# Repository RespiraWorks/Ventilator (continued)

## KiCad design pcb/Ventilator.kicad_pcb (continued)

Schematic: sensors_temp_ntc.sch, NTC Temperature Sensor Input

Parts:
C63: 10uF; C_1210_3225Metric; Voltage 100V; Manufacturer PN GRM32EC72A106KE05L
J31: Temperature sensor (NTC); Molex_Micro-Fit_3.0_43650-0215_1x02_P3.00mm_Vertical; Manufacturer PN 43650-0215
R102: 220 0.1%; R_0603_1608Metric; Manufacturer PN RG1608P-221-B-T5
R103: 10k 0.1%; R_0603_1608Metric; Manufacturer PN RG1608P-103-B-T5
U11: USBLC6-2SC6; SOT-23-6; Manufacturer PN USBLC6-2SC6

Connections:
+3.3V_Sns: R102.2, U11.5; also elsewhere on the board
GND: C63.2, R103.1, U11.2; also elsewhere on the board
unnamed: J31.1, U11.1
unnamed: J31.2, U11.3
unnamed: R102.1, U11.6

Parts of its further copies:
C60, C61, C62, C64: 10uF; C_1210_3225Metric; Voltage 100V; Manufacturer PN GRM32EC72A106KE05L
J32, J33, J34, J35: Temperature sensor (NTC); Molex_Micro-Fit_3.0_43650-0215_1x02_P3.00mm_Vertical; Manufacturer PN 43650-0215
R104, R106, R108, R110: 220 0.1%; R_0603_1608Metric; Manufacturer PN RG1608P-221-B-T5
R105, R107, R109, R111: 10k 0.1%; R_0603_1608Metric; Manufacturer PN RG1608P-103-B-T5
U12, U13, U14, U15: USBLC6-2SC6; SOT-23-6; Manufacturer PN USBLC6-2SC6

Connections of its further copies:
+3.3V_Sns: R104.2, R106.2, R108.2, R110.2, U12.5, U13.5, U14.5, U15.5; also elsewhere on the board
/System Monitor ADC/ADC1: C61.1, R105.2, U12.4; also elsewhere on the board
/System Monitor ADC/ADC2: C62.1, R107.2, U13.4; also elsewhere on the board
/System Monitor ADC/ADC4: C64.1, R111.2, U15.4; also elsewhere on the board
GND: C60.2, C61.2, C62.2, C64.2, R105.1, R107.1, R109.1, R111.1, U12.2, U13.2, U14.2, U15.2; also elsewhere on the board
unnamed: J32.1, U12.1
unnamed: J32.2, U12.3
unnamed: J33.1, U13.1
unnamed: J33.2, U13.3
unnamed: J34.1, U14.1
unnamed: J34.2, U14.3
unnamed: J35.1, U15.1
unnamed: J35.2, U15.3
unnamed: R104.1, U12.6
unnamed: R106.1, U13.6
unnamed: R108.1, U14.6
unnamed: R110.1, U15.6

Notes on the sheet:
LPF varies with temp (30hz at 150C, 3.1hz at 25C, 2.2hz at 0C) OK because of large margin between ADC sampling rate and desired sensor bandwidth
for 10k NTC B=3380K: @150C: R = 350 Vout = 3.12V Sensitivity: 2mV/degC @100C: R = 1022 Vout = 2.94V Sensitivity: 6mV/degC @25C: R = 10000 Vout = 1.63V Sensitivity: 30mV/degC @0C: R = 28255 Vout = 0.86V Sensitivity: 29mV/degC Temp (C) = B / ( ln( Vcc*10k/Vout/Rlim - (10k+220)/Rlim ) ) + 273.15 Where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
NTC placed on the high side of divider so that NTC missing or break does not drive ADC input to VCC Peak self-heating is 0.2mW, glass bead thermistor in air is about 1.5mW/degC, so this is a max error of 0.13degC due to self-heating.
Short current limit
150 nA max. leakage adds << 1 degree error across full temp. range

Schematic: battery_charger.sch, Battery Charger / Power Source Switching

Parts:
C98: 1nF; C_0603_1608Metric
C99, C109: 47nF; C_0603_1608Metric; Voltage 50V; Manufacturer PN C0603C473K5RACTU
C100, C101, C102, C111, C112, C113: 100nF; C_0603_1608Metric; Voltage 50V; Manufacturer PN C0603C104K5RACTU
C103, C106, C117: 10nF; C_0603_1608Metric; Voltage 50V; Manufacturer PN GRM1885C1H103JA01D
C104, C107, C116, C118, C119, C121, C122, C123, C124, C125: 10uF; C_1210_3225Metric; Voltage 100V; Manufacturer PN GRM32EC72A106KE05L
C105, C110: 1uF; C_0603_1608Metric; Voltage 50V; Manufacturer PN C0805C105K5RACTU
C108, C114, C115, C120: 100pF; C_0603_1608Metric; Voltage 50V; Manufacturer PN C0603C101J5GACTU
C126, C127: 33uF; CP_Elec_6.3x7.7; Voltage 50V; Manufacturer PN EEE-FK1H330XP
D27, D28: BAT54J; D_SOD-323F; Manufacturer PN BAT54J,115
HS1, HS2, HS3, HS4: Heatsink_Pad; Heatsink_Aavid_573100D00010G_HandSolder; Part Number 573100D00010G
L3: SRP1038A-3R3M; L_Bourns-SRP1038; Manufacturer PN SRP1038A-3R3M
Q16, Q17, Q18, Q19: BSC065N06LS5ATMA1; VSONP-8-1EP_5x6_P1.27mm; Manufacturer PN BSC065N06LS5ATMA1
Q20: SI7145DP-T1-GE3; VSONP-8-1EP_5x6_P1.27mm; Manufacturer PN SI7145DP-T1-GE3
R169: 442k; R_0603_1608Metric
R170, R172, R176: 100k; R_0603_1608Metric
R171, R175: 316k; R_0603_1608Metric
R173, R188: 0.01; R_1206_3216Metric; Manufacturer PN WSL1206R0100FEA
R174: 10; R_0603_1608Metric
R177, R178, R184, R186: 0; R_0603_1608Metric
R179, R180: 4.02k; R_0603_1608Metric
R181, R182, R185: 10k; R_0603_1608Metric
R183: 3M; R_0603_1608Metric
R187: 30.1k; R_0603_1608Metric
U23: BQ24773; QFN-28-1EP_4x4mm_P0.4mm_EP2.6x2.6mm_ThermalVias; Manufacturer PN BQ24773RUYR

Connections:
+3.3V_Ctrl: R181.2, R185.1; also elsewhere on the board
/CC-SCL: U23.12; also elsewhere on the board
/CC-SDA: U23.11; also elsewhere on the board
/PMon-ACOK: R185.2, U23.5; also elsewhere on the board
/PMon-PSys: C114.1, R187.1, U23.9; also elsewhere on the board
/Power Entry / Battery Handling/Battery Charger / Source Switching/Buck-In: C101.2, C102.1, C104.1, C107.1, HS3.1, Q18.3, R173.1, R177.1
/Power Entry / Battery Handling/Battery Charger / Source Switching/Pack-P: D27.2 (A), HS4.1, Q20.3, R175.1, U23.17; also elsewhere on the board
/Power Entry / Battery Handling/Battery Charger / Source Switching/RegN: C110.1, R171.1, R182.2, U23.24
/Power Entry / Battery Handling/Battery Charger / Source Switching/Vin-Adp-Swit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: C100.1, C101.1, HS2.1, Q17.3, R173.2, R178.2
/Power Entry / Battery Handling/PMon-IAdp: C120.1, U23.7; also elsewhere on the board
/Power Entry / Battery Handling/PMon-IBat: C115.1, U23.8; also elsewhere on the board
/Power Entry / Battery Handling/Power-Sw-P: C111.1, C113.1, C116.1, C117.1, C118.1, C119.1, C121.1, C122.1, C123.1, C124.1, C125.1, C126.1, C127.1, L3.2, R188.2, U23.20; also elsewhere on the board
/Power Entry / Battery Handling/Vin-Adp: C98.1, D28.2 (A), HS1.1, Q16.3, R169.1; also elsewhere on the board
GND: C100.2, C102.2, C103.2, C104.2, C105.2, C106.2, C107.2, C108.1, C110.2, C111.2, C112.1, C114.2, C115.2, C116.2, C117.2, C118.2, C119.2, C120.2, C121.2, C122.2, C123.2, C124.2, C125.2, C126.2, C127.2, Q19.1, R170.2, R172.2, R176.2, R187.2, U23.22, U23.29; also elsewhere on the board
unnamed: C98.2, C99.2, Q16.2, Q17.2, R179.2
unnamed: C99.1, Q16.1, Q17.1, R180.2
unnamed: C103.1, R171.2, R172.1, U23.21
unnamed: C105.1, R174.2, U23.28
unnamed: C106.1, R175.2, R176.1, R183.1, U23.13
unnamed: C108.2, Q19.2, U23.23
unnamed: C109.1, L3.1, Q18.1, Q19.3, U23.27
unnamed: C109.2, U23.25
unnamed: C112.2, C113.2, Q20.1, R188.1, U23.19
unnamed: D27.1 (K), D28.1 (K), R174.1
unnamed: Q18.2, U23.26
unnamed: Q20.2, R186.2
unnamed: R169.2, R170.1, U23.6
unnamed: R177.2, U23.1
unnamed: R178.1, U23.2
unnamed: R179.1, U23.4
unnamed: R180.1, U23.3
unnamed: R181.1, R183.2, R184.1, U23.14
unnamed: R182.1, U23.16
unnamed: R184.2, U23.15
unnamed: R186.1, U23.18

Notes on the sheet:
Design notes: - 6.3A max current, 17-20V input, approx 120W - Inductor selection: Isat 9.1A, 3.3uH - Wurth 7443330330 or Bourns SRP1038A-3R3M (OPL alt: MWSA1004-3R3MT) - Voltage will range from 12V to 16.8V for 4s Li-Ion battery - 11.5 to 13.0V for SLA (lead acid) - N-CH FET (30V, 3.3x3.3mm): CSD17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
V_ilim = 20*IPDM*Rac V_ilim = 1.29V -> 6.45A Note this is adapter current
Threshold here is 2.3V, max of 7V nBATPRES asserted when BAT_P over 9.6V Reused ILIM resistor values to reduce BOM.
Optional: R between CMPIN and CMPOUT sets hysteresis (not req'd when comparator polarity set to LOW)
PMON default is 1uA/W IBAT and IADT are voltage outputs
Vin-Adp used when >13V (ACDET pin > 2.4V)
0.4 or 0.8V/A from Vin_Adp (with 10mΩ ACP/N resistor)
0.2V/A charging, 0.8 or 1.6V/A discharging (with 10mΩ ACP/N resistor)
5.4V nominal
Optional heatsinks for Q16, Q17, Q18
Optional heatsink for Q20

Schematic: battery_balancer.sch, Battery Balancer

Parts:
C128, C134, C135, C136, C137: 10nF; C_0603_1608Metric; Voltage 50V; Manufacturer PN GRM1885C1H103JA01D
C129, C130, C131, C133: 470nF; C_0805_2012Metric; Voltage 50V; Manufacturer PN C0805C474K5RACTU
C132, C138: 100nF; C_0603_1608Metric; Voltage 50V; Manufacturer PN C0603C104K5RACTU
HS5, HS6: Heatsink_Pad; Heatsink_Aavid_573100D00010G_HandSolder; Part Number 573100D00010G
J46: BAT-BALANCE JST XH 5-pin; JST_XH_B5B-XH-A_1x05_P2.50mm_Vertical; Manufacturer PN B5B-XH-A(LF)(SN)
Q21, Q22: BSZ019N03LSATMA1; VSON-8-SGD_3.3x3.3mm_P0.65mm_NexFET; Manufacturer PN BSZ019N03LSATMA1
R189, R195: 1k; R_0603_1608Metric
R190: 2k; R_1206_3216Metric
R191: 10k; R_0603_1608Metric
R192, R193: 100; R_0603_1608Metric
R194, R200: 0.01; R_1206_3216Metric; Manufacturer PN WSL1206R0100FEA
R196, R197, R198, R199: 49.9; R_1206_3216Metric
R201: 10; R_0603_1608Metric
TH1: 10k; R_0603_1608Metric
U24: MAX17320G20+; WQFN-24-1EP_4x4mm_P0.5mm_EP2.6x2.6mm; Manufacturer PN MAX17320G22+

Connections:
/Bat-Alert: U24.7; also elsewhere on the board
/CC-SCL: U24.8; also elsewhere on the board
/CC-SDA: U24.9; also elsewhere on the board
/Power Entry / Battery Handling/Bat-N: C128.2, C129.2, C130.2, C131.2, C135.2, C138.2, R191.2, R194.1, R195.2, R200.1, TH1.2, U24.15, U24.20, U24.25; also elsewhere on the board
/Power Entry / Battery Handling/Bat-P: C132.1, Q22.1, R201.1; also elsewhere on the board
/Power Entry / Battery Handling/Battery Balancer/VMid: HS5.1, HS6.1, Q21.3, Q22.3
/Power Entry / Battery Handling/Battery Charger / Source Switching/Pack-P: Q21.1, R189.1, R190.2; also elsewhere on the board
GND: R194.2, R200.2, U24.14; also elsewhere on the board
unnamed: C128.1, R189.2, U24.6
unnamed: C129.1, U24.13
unnamed: C130.1, U24.17
unnamed: C131.1, R191.1, U24.12
unnamed: C132.2, Q22.2, R193.1
unnamed: C133.1, U24.2
unnamed: C133.2, C138.1, R201.2, U24.1
unnamed: C134.1, C136.2, R197.1, U24.23
unnamed: C134.2, C137.1, R198.1, U24.22
unnamed: C135.1, C137.2, R199.1, U24.21
unnamed: C136.1, R196.1, U24.24
unnamed: J46.2, R199.2
unnamed: J46.3, R198.2
unnamed: J46.4, R197.2
unnamed: J46.5, R196.2
unnamed: Q21.2, R192.1
unnamed: R190.1, U24.5
unnamed: R192.2, U24.4
unnamed: R193.2, U24.3
unnamed: R195.1, U24.11
unnamed: TH1.1, U24.10

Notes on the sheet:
IC max balancing current: 100mA Set balancing current: 71mA = 4.2V cell voltage / (49.9Ω + 9Ω internal)
Battery Balancing Connector
Max. recovery charge current = Vin/(2K+10) = 8.5 mA @ 17 Vin
5mΩ: 5-155 mV short-circuit threshold = 1-31 A 2.5-77.5 mV medium over-discharge threshold = 0.5-15.5 A 0-51.2 mV slow over-discharge threshold = 0-10.24 A 0-38.75 mV charge threshold = 0-7.75 A
I2C address: 0b01100110 and 0b0001110
Optional heatsinks for Q21, Q22

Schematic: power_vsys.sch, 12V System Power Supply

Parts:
C139: 2.7nF; C_0603_1608Metric; Voltage 50V; Manufacturer PN C0603C272J5GACTU
C140, C147: 100pF; C_0603_1608Metric; Voltage 50V; Manufacturer PN C0603C101J5GACTU
C141, C143, C149, C150, C152, C153: 10uF; C_1210_3225Metric; Voltage 100V; Manufacturer PN GRM32EC72A106KE05L
C142, C146, C148: 100nF; C_0603_1608Metric; Voltage 50V; Manufacturer PN C0603C104K5RACTU
C144, C145: 220nF; C_0805_2012Metric; Voltage 100V; Manufacturer PN C0805C224K1RACTU
C151, C154: 1uF; C_0603_1608Metric; Voltage 50V; Manufacturer PN C0805C105K5RACTU
D29: BAT54J; D_SOD-323F; Manufacturer PN BAT54J,115
HS7: Heatsink_Pad; Heatsink_Aavid_573100D00010G_HandSolder; Part Number 573100D00010G
L4: 6.8uH; L_TDK_SPM12565VT; Manufacturer PN SPM12565VT-6R8M-D
NT1: Net-Tie_2; NetTie-2_SMD_Pad0.5mm
Q23: MMBT3904; SOT-23; Manufacturer PN MMBT3904-7-F
Q24, Q25: BSZ019N03LSATMA1; VSON-8-SGD_3.3x3.3mm_P0.65mm_NexFET; Manufacturer PN BSZ019N03LSATMA1
R202, R203, R204, R205, R207, R213, R215: 10k; R_0603_1608Metric
R206: 6.49k; R_0603_1608Metric
R208: 52.3k; R_0603_1608Metric
R209, R210: 10; R_0603_1608Metric
R211: 0.006; R_1206_3216Metric; Manufacturer PN TLR2B10DR006FTDG
R212: 100k; R_0603_1608Metric
R214: 1M; R_0603_1608Metric
U25: LM5141; VQFN-24-1EP_4x4mm_P0.5mm_EP2.45x2.45mm_ThermalVias; Manufacturer PN LM5141RGER

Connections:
+3.3V_Ctrl: R215.1; also elsewhere on the board
+12V: C147.2, C149.1, C150.1, C152.1, C153.1, R211.1, R212.1, R214.1, U25.17; also elsewhere on the board
+VLink: C141.1, C143.1, HS7.1, Q24.3, R207.1, U25.15; also elsewhere on the board
/Power Entry / Battery Handling/12V System Buck Converter/LM5141-AGND: C140.2, C142.1, C144.1, C145.1, C148.2, NT1.1, R204.2, R206.2, R208.2, U25.3, U25.6
/Power Entry / Battery Handling/12V System Buck Converter/LM5141-VCC: C151.2, C154.2, D29.2 (A), U25.10
/Power Entry / Battery Handling/12V System Buck Converter/LM5141-VDDA: C148.1, R203.1, U25.2
/Power Entry / Battery Handling/PG-12V: R215.2, U25.21; also elsewhere on the board
/VSys-Power-Off: R202.2; also elsewhere on the board
GND: C141.2, C143.2, C149.2, C150.2, C151.1, C152.2, C153.2, C154.1, NT1.2, Q23.2, Q25.1, R205.1, R213.2, U25.9, U25.16, U25.25; also elsewhere on the board
unnamed: C139.1, C140.1, U25.20
unnamed: C139.2, R206.1
unnamed: C142.2, U25.22
unnamed: C144.2, U25.24
unnamed: C145.2, U25.5
unnamed: C146.1, L4.1, Q24.1, Q25.3, U25.12
unnamed: C146.2, D29.1 (K), U25.11
unnamed: C147.1, L4.2, R211.2, U25.18
unnamed: Q23.1, R202.1, R205.2
unnamed: Q23.3, R207.2, U25.23
unnamed: Q24.2, R210.2, U25.14
unnamed: Q25.2, R209.2, U25.7
unnamed: R203.2, R204.1, U25.1
unnamed: R208.1, U25.4
unnamed: R209.1, U25.8
unnamed: R210.1, U25.13
unnamed: R212.2, R213.1, R214.2, U25.19

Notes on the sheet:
12.5-16.8V IN
Cycle-by-cycle current limit: 75mA -> 12.5A
Forced-PWM CCM mode @ light load
Diode emulation mode @ light load
440 kHz fsw nominal
220nF modulates fsw +/- 5% @ ~~380 Hz
53.2k fine-tunes fsw = 422 kHz nominal
Soft-start time = 1.2V*100nF/20uA = 6 ms
= 90.9k, to reduce BOM
Regulates @ FB = 1.2V; Nom. 12.1V out
Optional heatsink for Q24

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
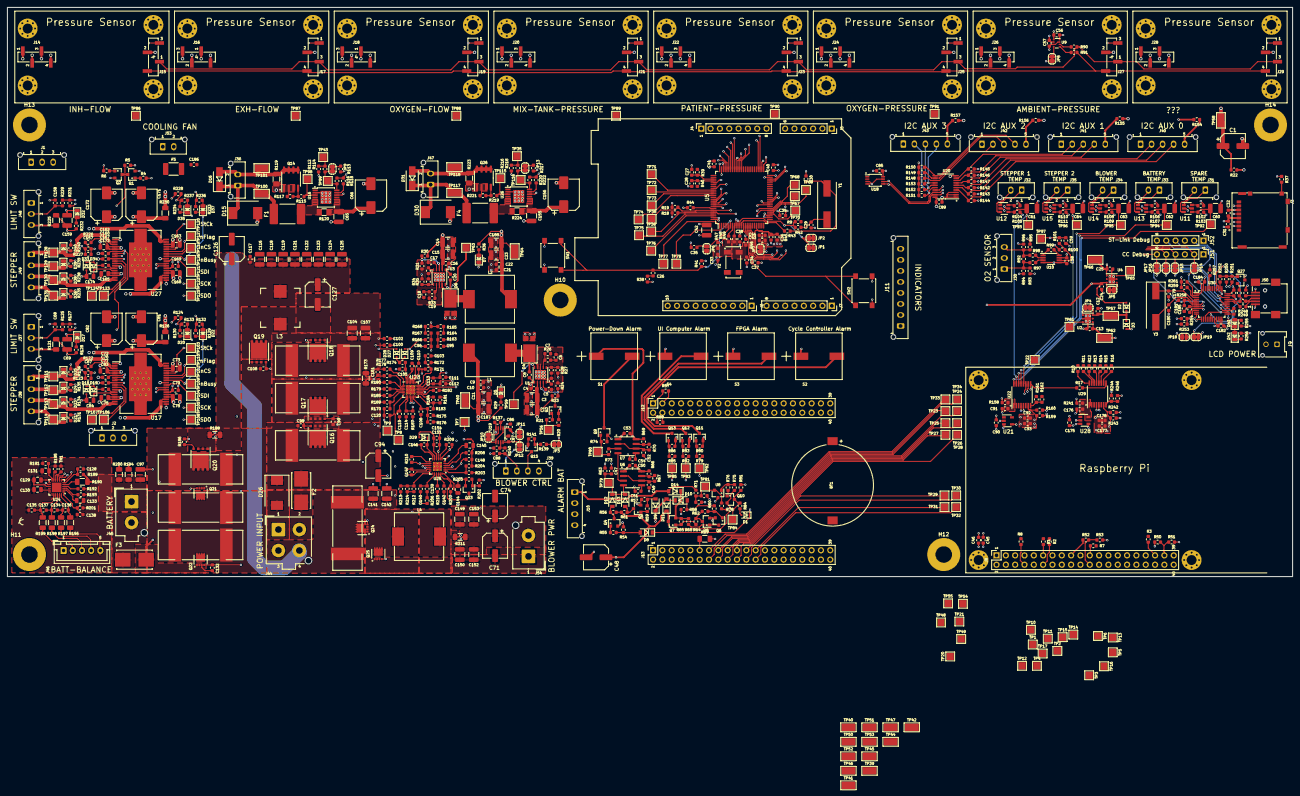
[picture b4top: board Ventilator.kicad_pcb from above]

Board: 4 copper layers, 350.0 x 155.0 mm, 787 parts (1 on the bottom side), 429 nets.

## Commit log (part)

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2022-06-22 make distinct subclasses to SW vs DMA uart Channels
2022-06-22 change comms way to handle transfers to allow Rx to be handled by DMA
2022-06-22 clang-format hook
2022-06-22 Update README.md
    Added clarifying notes about the first run wizard option in imager. Changed the Raspberry Pi OS version to match the newer naming convention, and removed the release date so these instructions won't 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
2022-06-23 tubing run for 60 degree config created, needs barbs still; updates #1019
    Began work on barbs, parametrization, updates #1019
    tweaked barb end, will need to fix alignment
    tweaked barb end, will need to fix alignment
    tweaked barb end, will need to fix alignment
    tweaked barb end, will need to fix alignment
    added second barb, needs better parametrization, updates #1019
2022-06-23 Renderings
    2 Ventilator renderings in empty space. One rendering in a hospital room.
    Added 2 empty room, 1 at hospital render. Hospital render scale is not right, will change it.
    "only hospital jpg should be kept; updates #1160"
    "only hospital jpg should be kept; updates #1160"
2022-06-24 adding wireviz YAML file for power entry harness
2022-06-24 adds item A25 to the BOM: 4.7mm QC terminal for main power harness
2022-06-24 corrections based on comments from @dcstraney: kycon receptacle pinout updated and image added to clarify for assembly.
2022-06-26 adding wireviz YAML file for power entry harness
    modified to use pre-crimped leads
    corrections based on comments from @dcstraney: kycon receptacle pinout updated and image added to clarify for assembly.
    updates Main Power harness readme documentation for V0.4
    adds item A25 to the BOM: 4.7mm QC terminal for main power harness
    adding link to google drive
    added pinout image
2022-06-26 documentation updates and directory move-arounds (#1258)
2022-06-28 Add framing to messages exchanged between controller and gui: (#1225)
    - now include a crc32 checksum
    - are now framed with start/end of frame markers (escaped if necessary)
    Remove stm32-uart environment, along with UART_VIA_DMA build option
    Add proper scope delimiters to all if / for / while in controller code (per review comment)
    Keep googletest back to v1.11.0
2022-07-01 Refactor breath detection to make it usable outside of pressure assist mode
2022-07-03 Add breath detection simple tests.
2022-07-04 adding #includes in integration_test/main in order to fix new regression in pio's ldf
2022-07-04 Fix code coverage issue (#1272)
    upgrade to pio 6.1.0, which enables coverage reports again
2022-07-05 "squash gh-pages history; updates #1267"
    "syntax tweaks; updates #1267"
    "deploy only on master; updates #1267"
2022-07-06 Remove temporary patches now platformio 6.1 is fixed and released (#1276)
    upgrade to latest ststm32 platform
2022-07-07 adding gh action build workflow for sonar
2022-07-07 "more sonar config; updates #909"
2022-07-07 initial modifications to venturi; update #1199
2022-07-11 Add README.md file
    Add README.md with instructions on generating network protocol
2022-07-12 Updated network protocol outputs
2022-07-13 battery: parameterize and apply best practices
2022-07-14 added yml file
2022-07-15 "Further refactoring of HAL and main controller loop; updates #1184"
    "further decouple clocks and gpio in HAL; updates #1184"
    "precommit reformat; updates #1184"
    "update headers; updates #1184"
    "templated sensor classes; updates #1184"
    "abstracted Sensors class and disentangled sensor tests; updates #1184"
    "some cleanup and abstraction of actuators container; updates #1184"
2022-07-15 code style and other cleanup
2022-07-15 fixed controls.qrc
2022-07-15 created nested flow control for pinch valve during fio2 60-100%. Working demo of continuous fio2 control from 21 to 100%
2022-07-15 a bit of cleanup
2022-07-17 move network protocols from generate to install
2022-07-21 Revert "Updated network protocol outputs"
    This reverts commit f93b6444118eea162cfdbd19eb9a70df11c34f72.
2022-07-22 Add unit tests to spi chain
2022-07-22 Fix formatting and fix stepper (stub) unit test
2022-07-24 Add a busy wait to force CS to stay low after sending bytes on SPI daisy chain
2022-07-28 fix dead link in manufacturing page
2022-07-30 "HAL refactoring: HighPriorityTrigger and SysControl; updates #1184" (#1288)
    "moved pcb pins to system implementation, clocks as namespace, cleanup; updates #1184"
    "factored out processor constants and partially latency tracker; updates #1184"
    "timers refactoring; updates #1184"
    "factored out high priority trigger; updates #1184"
    "precommit reformat; updates #1184"
    fix after rebasing
2022-07-30 "new function implementation; updates #1184"
2022-07-30 "using new approach; updates #1184"
2022-07-31 fix some static checker warnings
2022-07-31 "debug comms using new callback; updates #1293"
2022-08-01 pressure sensor mod
2022-08-01 fix static checks warnings and integration tests
2022-08-09 var_info already has typechecking, removing from controller_debug
2022-08-09 removed re dependency
2022-08-09 floatarrays show linearity in get var
2022-08-09 removed some automatically added redundant dependencies, cleaned up TODOs
2022-08-09 simplified eval() call by creating a scoped_eval function
2022-08-09 print error message without printing stack trace
2022-08-09 better errors to user for input mistakes, DebugFunctions return arrays, and type checking input
2022-08-09 unit testing debug_cli helper functions and adding tests to CI
2022-08-09 using eval() to process input data for set var
2022-08-09 refactored float array analysis out of print var function
2022-08-09 print errors in red; check variable type using constant defined in varinfo
2022-08-11 "script generates serialization code; updates #1263"
    "fixed bad link and updated dependencies; updates #1263"
    "dependencies; updates #1263"
    "dependencies; updates #1263"
    "script should work now; updates #1263"
    "show pip locations; updates #1263"
    "get dir a different way; updates #1263"
2022-08-11 "vent number is now string; updates #376"
    "updated debugger; updates #376"
    "string conversion; updates #376"
    "fixed string serialization; updates #376"
    "unit tests fixed; updates #376"
    "addressed review; updates #376"
    "removed dead link; updates #376"
2022-08-12 Temporary fix for #1298, not blocking interrupts when high priority loop queues data to the stepper SPI chain (#1305)
    More rationales can be found in the code.
2022-09-24 PR#1308: adding python3-pip to docs.sh install list
2022-09-26 Documentation scripts improved, especially for wiring assemblies (#1308)
    * wiring documentation scripts accomodate more assemblies, convenient docs generation bash utility; updates #1260
    * Update docs/docs.sh
    * Update docs/docs.sh
    * PR#1308: adding python3-pip to docs.sh install list
    * reintroduced docs branch condition and fixed ali links; updates #1260
    * added aliexpress to liche exclude; updates #1260
2022-10-01 added some documentation; updates #1303
2022-10-02 smarter device detection and connection routines; updates #1303
2022-10-03 cleanup; updates #1303
2022-10-04 some restructuring of debug libs; updates #1303
2022-10-04 debugger works without manifest; updates #1303
2022-10-05 controller obeys SN variable when calling debugger; updates #1303
2022-10-09 Single device manifest for both controller deployment and debug interface (#1304)
    * controller script does all integration functions; updates #1303
    * ocd patching; updates #1303
    * more clever debug port scans; updates #1303
    * added some documentation; updates #1303
    * smarter device detection and connection routines; updates #1303
    * move manifest to gdrive; updates #1303
2022-10-18 corrected pricing units for part ew-24awg-kit
2022-10-18 scripts updated
    fixed docs deployment script
    fixed docs deployment script
    fixed docs deployment script
    fixed docs deployment script
    fixed docs deployment script
2022-10-18 Corrects PR#1287: 24awg wire kit part selection
2022-10-22 new link checker in gh workflows; updates #1313
2022-10-22 more excludes; updates #1313
2022-10-22 docs generation workflow only on push; updates #1313
2022-10-27 Update link checker (#1315)
    * new link checker in gh workflows; updates #1313
    * always build docs but push only on master; updates #1313
    * more excludes; updates #1313
    * more excludes; updates #1313
    * simplified workflows, removed link checker from circleci, updated documentation; updates #1313
    * simplified circleci pipelines; updates #1313
2022-11-01 added whitespace for consistency with readme
2022-11-03 added readme
2022-11-15 updated ubuntu image tags; updates #1319
2022-11-15 apply fix to all jobs; updates #1319
2022-11-21 adds an offset parameter to control the pressfit shaft opening size #1322 #1121
2022-11-22 updated parts.json with link to 12V version of tkfan blower, PR #1317
2022-11-22 updated blower harness instructions per PR #1317
2023-01-17 added jenkinsfile; updates #1309
2023-01-18 more steps; updates #1309
2023-01-18 print branch info; updates #1309
2023-01-18 escape sequences; updates #1309
2023-01-19 better cleanup of docker images; updates #1309
2023-01-19 correct code root path; updates #1309
2023-01-20 added some more docker crap; updates #1309
2023-01-22 wrangling pt 2: correctly copying the repo
2023-01-22 wrangling pt 4: correctly copying the repo
2023-01-22 wrangling pt 8: correctly copying the repo
2023-02-12 Add more counter for abnormal conditions
2023-03-21 locked conan to 1.59 for now; updates #1324
2023-03-21 Functionally complete back-panel for v0.4 prototypes
    expanded then acrylic design
    unnecessary superflous files
    relocated usb and power connector
    moved screws around and added Ethernet cutout
    enlarged cutouts for fit
    files I forgot to save before my previous commmit
2023-04-01 platformio udev URL update; updates #1324
2023-04-01 lychee config file update; updates #1324
2023-04-02 "oops"
2023-04-02 "debug interface improvements and compatibility with newer compilers"
2023-04-03 Platformio version bump (#1328)
    * "bump pio verison"
    * "debug interface improvements and compatibility with newer compilers"
    * "more syntax checks in controller script"
    * "oops"
    * "Helpful instructions when doing integraton tests"
    * "simplified controller readme"
2023-04-04 refactoring and cleanup; updates #1329
2023-04-04 cleanup and install scripts for qt6; updates #1329
2023-04-04 no qt in conan; updates #1329
2023-04-04 some progress, but broken; updates #1300
2023-04-11 Remove qnanopainter submodule (#1331)
    * got rid of qnanopainter; updates #1329
    * works!; updates #1329
    * refactoring and cleanup; updates #1329
    * no need to deal with submodules in build scripts; updates #1329
    * gui demo desktop shortcut; updates #1329
    * reenabled time_series_graph tests; updates #1329
2023-04-11 Nanopb libs brought in as platformio package (#1333)
    * nanopb brought in as pio package; updates #1301
    * gui run does not need to generate protocols; updates #1301
2023-04-12 fewer badges
2023-04-17 removed token from repo, removed codecov pip package install (#1335)
    Critical fix. CI builds broken.
2023-04-26 Parameterized blower adapter CAD (#1307)
    folding in unnecessarily changed files from upstream; updates #940
    internals as iAssembly, slim fan, acrylic cutouts for blower; updates #940
    spacers in blower designs, air inlet angle and height optimized, inlet tube diameter fixed, tkfan retainer improved, cooling fan assembly with guard; updates #940
    tk blower assembly: better labeling, additional vertical offset for shrinkage; updates #940
    part and feature renaming, some files culled; updates #940
    updated TKFan purchase link; updates #940
2023-04-26 pinch valve simplification, more components in pneumatics assy; updates #1252
2023-09-05 non-interactive install
2023-09-11 initial design of new base plate
2024-05-05 update codecov script
2024-05-05 les do dis
2024-05-05 controller upload coverage new way
2024-05-05 bump conan ant build GUI
2024-05-06 cleanup
2024-05-06 cov cleanup
2024-05-06 Deploying to gh-pages from @ RespiraWorks/Ventilator@20104be86f80c81cdc6aad84716711599d8f6f05 🚀
2024-10-23 pipx ensure path
2024-10-23 fixed comon test and moved debugger
2024-10-27 updated wiring generation scripts
2024-10-27 exclude siargo links from checker
2024-10-29 fixup
2024-10-31 more refactoring and lib bumps
2024-11-01 docs lychee as part of script
2024-11-03 run docker non interactive
2024-11-03 fix gui build
2024-11-09 fix update script
2024-11-09 update bootstrap docs for new raspi os, install ocd-patch during update
2024-11-10 Deploying to gh-pages from @ RespiraWorks/Ventilator@ec1e567c2e8828d9ca41fcc54afcd5f82de95a83 🚀
